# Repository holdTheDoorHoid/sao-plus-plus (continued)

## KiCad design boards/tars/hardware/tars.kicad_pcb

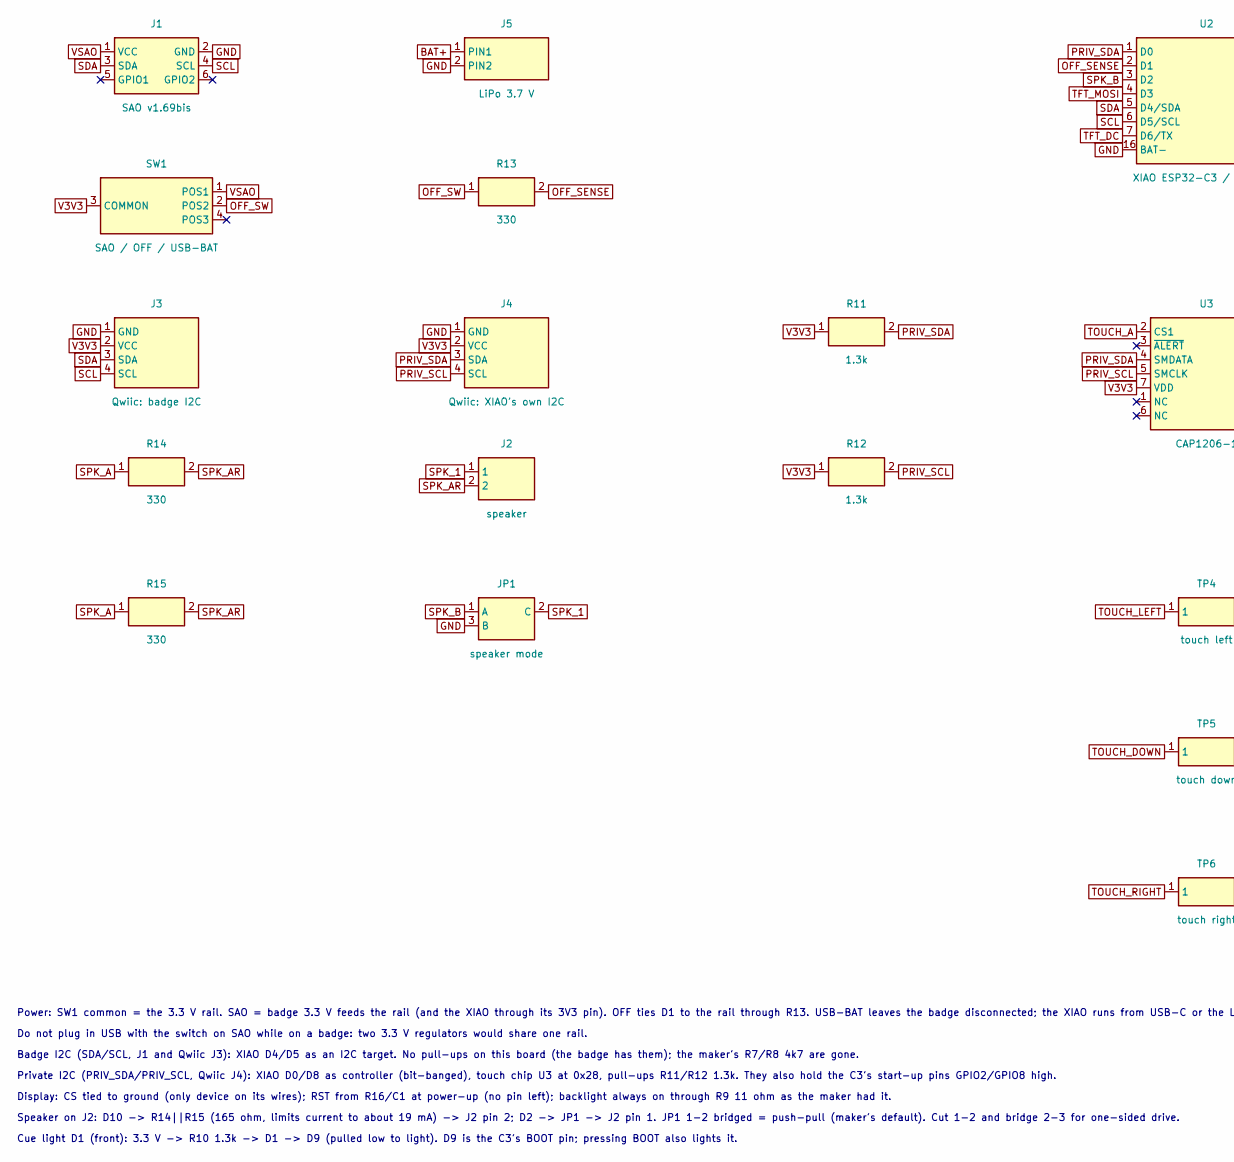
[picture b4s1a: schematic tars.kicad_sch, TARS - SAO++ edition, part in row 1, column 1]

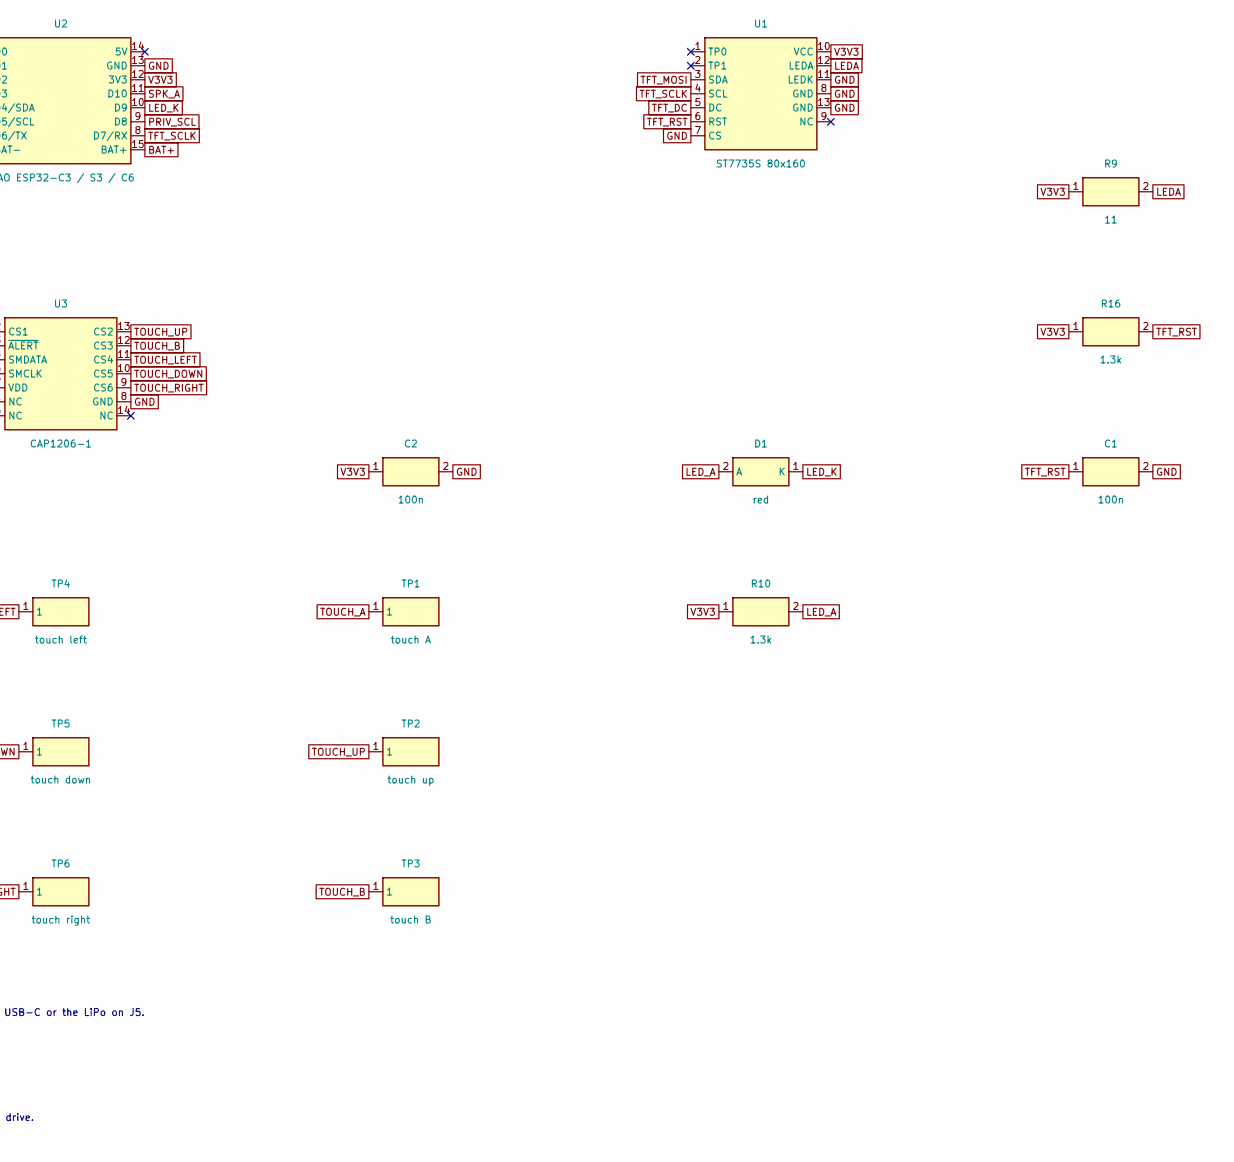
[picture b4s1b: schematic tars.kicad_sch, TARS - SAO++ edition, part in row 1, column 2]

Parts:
C1, C2: 100n; SAOPP_C_0603_1608Metric; MPN CC0603KRX7R9BB104; LCSC C14663
D1: red; LED_0603_1608Metric_Pad1.05x0.95mm_HandSolder; MPN LTST-C191KRKT; LCSC C125099
J1: SAO v1.69bis; SAOPP_CONN-01_BoxHeader_2x03_P2.54mm_SMD_XFCN_BH254VS-6P; MPN BH254VS-6P; LCSC C492445
J2: speaker; Molex_PicoBlade_53261-0271_1x02-1MP_P1.25mm_Horizontal; MPN 53261-0271; LCSC C177225
J3: Qwiic: badge I2C; JST_SH_SM04B-SRSS-TB_1x04-1MP_P1.00mm_Horizontal; MPN SM04B-SRSS-TB(LF)(SN); LCSC C160404
J4: Qwiic: XIAO's own I2C; JST_SH_SM04B-SRSS-TB_1x04-1MP_P1.00mm_Horizontal; MPN SM04B-SRSS-TB(LF)(SN); LCSC C160404
J5: LiPo 3.7 V; SAOPP_CONN-10_JST_PH_S2B-PH-SM4-TB_1x02_Horizontal; MPN S2B-PH-SM4-TB(LF)(SN); LCSC C295747
JP1: speaker mode; SolderJumper-3_P1.3mm_Bridged12_RoundedPad1.0x1.5mm; MPN none: solder jumper, nothing fitted
R9: 11; R_0603_1608Metric; MPN 0603WAF110JT5E
R10, R11, R12, R16: 1.3k; SAOPP_R_0603_1608Metric; MPN 0603WAF1301T5E; LCSC C22767
R13, R14, R15: 330; SAOPP_R_0603_1608Metric; MPN 0603WAF3300T5E; LCSC C23138
SW1: SAO / OFF / USB-BAT; SAOPP_SW-01_Slide_SP3T_CK_PCM13SMTR; MPN PCM13SMTR; LCSC C221842
TP1: touch A; TestPoint_Pad_D1.0mm; MPN none: bare copper inside a touch pad
TP2: touch up; TestPoint_Pad_D1.0mm; MPN none: bare copper inside a touch pad
TP3: touch B; TestPoint_Pad_D1.0mm; MPN none: bare copper inside a touch pad
TP4: touch left; TestPoint_Pad_D1.0mm; MPN none: bare copper inside a touch pad
TP5: touch down; TestPoint_Pad_D1.0mm; MPN none: bare copper inside a touch pad
TP6: touch right; TestPoint_Pad_D1.0mm; MPN none: bare copper inside a touch pad
U1: ST7735S 80x160; ST7735S-160x80-13PIN; MPN 0.96 in 80x160 ST7735S IPS, 13-pin 0.7 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
U2: XIAO ESP32-C3 / S3 / C6; SAOPP_MCU-01_Seeed_XIAO_SMD_C3_S3_C6; MPN XIAO ESP32-C3 / S3 / C6
U3: CAP1206-1; SOIC-14_3.9x8.7mm_P1.27mm; MPN CAP1206-1-SL-TR; LCSC C2652106

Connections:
BAT+: J5.1 (PIN1), U2.15 (BAT+)
GND: C1.2, C2.2, J1.2 (GND), J3.1 (GND), J4.1 (GND), J5.2 (PIN2), JP1.3 (B), U1.7 (CS), U1.8 (GND), U1.11 (LEDK), U1.13 (GND), U2.13 (GND), U2.16 (BAT-), U3.8 (GND)
LEDA: R9.2, U1.12 (LEDA)
LED_A: D1.2 (A), R10.2
LED_K: D1.1 (K), U2.10 (D9)
OFF_SENSE: R13.2, U2.2 (D1)
OFF_SW: R13.1, SW1.2 (POS2)
PRIV_SCL: J4.4 (SCL), R12.2, U2.9 (D8), U3.5 (SMCLK)
PRIV_SDA: J4.3 (SDA), R11.2, U2.1 (D0), U3.4 (SMDATA)
SCL: J1.4 (SCL), J3.4 (SCL), U2.6 (D5/SCL)
SDA: J1.3 (SDA), J3.3 (SDA), U2.5 (D4/SDA)
SPK_1: J2.1, JP1.2 (C)
SPK_A: R14.1, R15.1, U2.11 (D10)
SPK_AR: J2.2, R14.2, R15.2
SPK_B: JP1.1 (A), U2.3 (D2)
TFT_DC: U1.5 (DC), U2.7 (D6/TX)
TFT_MOSI: U1.3 (SDA), U2.4 (D3)
TFT_RST: C1.1, R16.2, U1.6 (RST)
TFT_SCLK: U1.4 (SCL), U2.8 (D7/RX)
TOUCH_A: TP1.1, U3.2 (CS1)
TOUCH_B: TP3.1, U3.12 (CS3)
TOUCH_DOWN: TP5.1, U3.10 (CS5)
TOUCH_LEFT: TP4.1, U3.11 (CS4)
TOUCH_RIGHT: TP6.1, U3.9 (CS6)
TOUCH_UP: TP2.1, U3.13 (CS2)
V3V3: C2.1, J3.2 (VCC), J4.2 (VCC), R9.1, R10.1, R11.1, R12.1, R16.1, SW1.3 (COMMON), U1.10 (VCC), U2.12 (3V3), U3.7 (VDD)
VSAO: J1.1 (VCC), SW1.1 (POS1)

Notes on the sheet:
Power: SW1 common = the 3.3 V rail. SAO = badge 3.3 V feeds the rail (and the XIAO through its 3V3 pin). OFF ties D1 to the rail through R13. USB-BAT leaves the badge disconnected; the XIAO runs from USB-C or the LiPo on J5.
Do not plug in USB with the switch on SAO while on a badge: two 3.3 V regulators would share one rail.
Badge I2C (SDA/SCL, J1 and Qwiic J3): XIAO D4/D5 as an I2C target. No pull-ups on this board (the badge has them); the maker's R7/R8 4k7 are gone.
Private I2C (PRIV_SDA/PRIV_SCL, Qwiic J4): XIAO D0/D8 as controller (bit-banged), touch chip U3 at 0x28, pull-ups R11/R12 1.3k. They also hold the C3's start-up pins GPIO2/GPIO8 high.
Display: CS tied to ground (only device on its wires); RST from R16/C1 at power-up (no pin left); backlight always on through R9 11 ohm as the maker had it.
Speaker on J2: D10 -> R14||R15 (165 ohm, limits current to about 19 mA) -> J2 pin 2; D2 -> JP1 -> J2 pin 1. JP1 1-2 bridged = push-pull (maker's default). Cut 1-2 and bridge 2-3 for one-sided drive.
Cue light D1 (front): 3.3 V -> R10 1.3k -> D1 -> D9 (pulled low to light). D9 is the C3's BOOT pin; pressing BOOT also lights it.

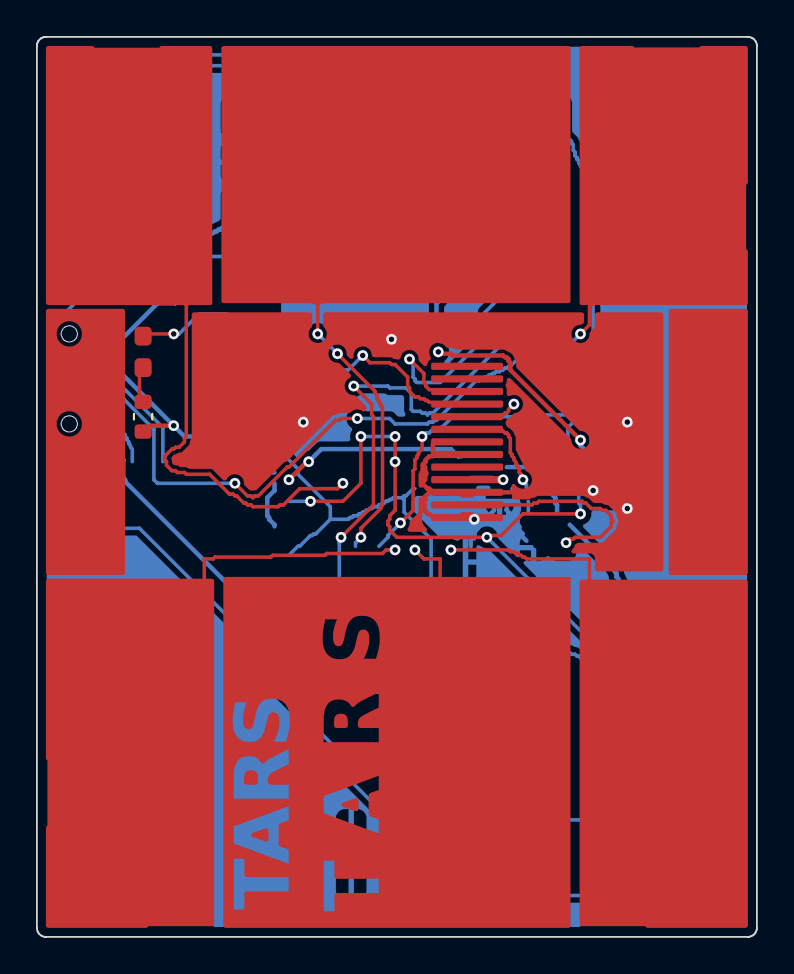
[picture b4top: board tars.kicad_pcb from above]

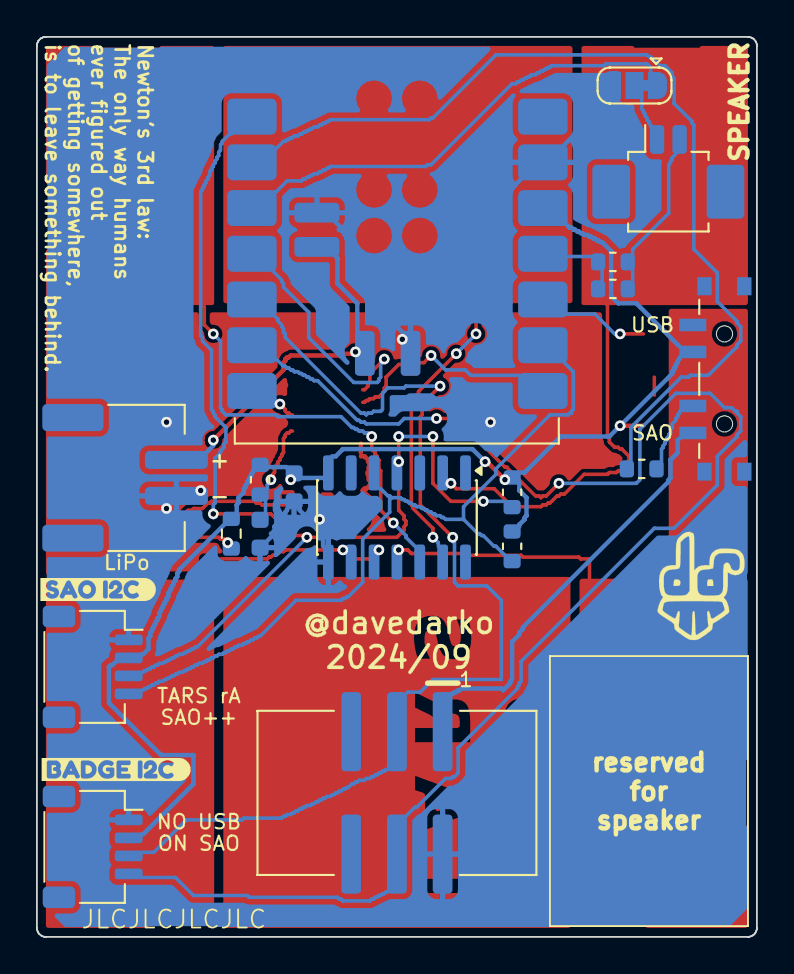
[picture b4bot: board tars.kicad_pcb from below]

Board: 2 copper layers, 40.0 x 50.0 mm, 30 parts (21 on the bottom side), 27 nets.

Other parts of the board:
Ref**: Val**; davedarko_logo_silk_outline
kibuzzard-66F128E4: G***; kibuzzard-66F128E4
kibuzzard-66F12846: G***; kibuzzard-66F12846

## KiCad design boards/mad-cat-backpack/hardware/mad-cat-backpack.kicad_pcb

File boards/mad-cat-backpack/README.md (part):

# Mad Cat Backpack — SAO++ edition

Originally the **Mad Cat Backpack** by **Wireb (Peter Shabino)**, 2018: https://github.com/Wireb/Mad_Cat_Backpack (commit f247c92). It is a small board that is soldered flat against the **back** of TwinkleTwinkie's Mad Cat SAO and makes the cat's eyes and teeth move: they fade, blink, "talk", lick their lips and sparkle.

> **Open licence (MIT).** The maker's design and firmware are MIT-licensed, so they may be copied, changed and sold, as long as his notice goes with them:
>
> *Copyright (c) 2018 Peter Shabino.* Permission is hereby granted, free of charge, to any person obtaining a copy of this hardware, software, and associated documentation files (the "Product"), to deal in the Product without restriction, including without limitation the rights to use, copy, modify, merge, publish, distribute, sublicense, and/or sell copies of the Product, and to permit persons to whom the Product is furnished to do so, subject to the following conditions: The above copyright notice and this permission notice shall be included in all copies or substantial portions of the Product. THE PRODUCT IS PROVIDED "AS IS", WITHOUT WARRANTY OF ANY KIND (full text: [original/LICENSE](original/LICENSE)).
>
> **Two things that are not his to license.** The little icon he drew on the back is a **Metroid**, a Nintendo character; it is kept exactly as he drew it, and whether to keep it is the owner's call. And this board exists to light **TwinkleTwinkie's Mad Cat** ([../mad-cat](../mad-cat)), whose own permission is still pending: this board carries none of the Mad Cat's art (only its outline and LED positions), but it is no use without one.

The renders show this board alone. The "front" is the side that is pressed against the back of the Mad Cat, so in use it is never seen; all the parts are on the other side, facing the badge.

## How it goes together with the Mad Cat

1. Build an SAO++ Mad Cat (**boards/mad-cat**) as a **bare board: fit none of its parts** (no connector, switch, cell clip, LEDs or resistors). It becomes the face plate.
2. Lay the bare Mad Cat face down and put this board on its back, parts side up. Line them up: each of this board's eight 1.0 mm light holes sits over one of the Mad Cat's bare eye or tooth windows, and the outlines match (this board is the Mad Cat's own outline, 0.35 mm smaller all round, so nothing shows from the front).
3. Solder the **eight bond holes** (the bare gold rings beside the eyes and the two middle-left teeth) from this side: solder fed into each hole runs down and joins the Mad Cat's unused LED pad underneath.
4. Plug the pair into a badge with this board's connector. It sits exactly where a plain Mad Cat's connector would, so the cat hangs the same way, just 1.6 mm further out.

The maker did the same thing in 2018 with an unmodified Mad Cat: he moved its eight LEDs onto his backpack, cut four of the Mad Cat's traces, and soldered four pads under the backpack's edge. On the SAO++ Mad Cat nothing has to be cut: leaving its parts off is enough.

**Can our Mad Cat still be driven by it?** Yes, that is what it is built for: the SAO++ Mad Cat kept the 2018 LED positions, and its back copper is already cleared around each one, so this board's LEDs shine through the same windows the Mad Cat's own LEDs would. A **2018** Mad Cat (with its LEDs and header removed) should light up the same way, but the bond holes would not land on its pads (its LED pads are 2.4 mm from each centre, not 1.55 mm), so it would need glue instead of solder. That has not been checked.

## What changed from the original

| | Original (2018) | SAO++ rev A |
|---|---|---|
| Size and shape | 33.5 × 31.2 mm plate behind the face only | **63.0 × 39.0 mm**: the Mad Cat's own outline, 0.35 mm smaller all round, covering the face, the haunch and the root of the tail. Bigger because the XIAO module (21 × 18 mm) does not fit behind the face with the eight LEDs |
| Controller | PIC16F1503 | **Seeed Studio XIAO ESP32** (C3, S3 or C6) on the back of the haunch, USB-C at the haunch's right-hand edge |
| Firmware | his PIC assembly | **new Rust firmware** that replays his eight animations with his timing and his random weights ([firmware/](firmware/)) |
| LEDs | the eight white TOPLEDs taken off the Mad Cat, on the side facing the cat | eight white **reverse-mount** LEDs (the shared SAO++ part) on the back, each over a 1.0 mm hole; same eight spots, same order |
| LED resistors | 8 × 200 Ω 0805 | 8 × **330 Ω** 0603 (shared part): about 1.5 mA per LED on 3.3 V, much like his board on badge power (he warned 200 Ω was "borderline too bright" on 5 V USB) |
| Power and connector | 4-pin header pushed through both boards (badge power), or his mini-USB socket | **6-pin SAO v1.69bis** shrouded connector on the back, in the Mad Cat connector's exact spot; **SAO / OFF / USB-BAT** slide switch with its knob out of the bottom edge under the left paw; **LiPo socket** (JST-PH) at the root of the tail, charged by the XIAO |
| Joining the boards | four pads soldered under the backpack's edge, four Mad Cat traces cut | **eight bond holes** over eight unused Mad Cat LED pads; nothing cut |
| I2C | none (his SDA/SCL holes went nowhere) | the XIAO is an I2C target at **0x24**: a badge can set the LEDs or start any animation |
| Dropped | — | the PIC, its programming header, mini-USB socket and 10 µF capacitor (the XIAO has its own) |
| Maker's art | "Mad Cat Backpack / PJS 17Oct2018 V0 / MIT license" lettering and a Metroid icon, both on the back near the old 4-pin header | **Both kept, unchanged in wording, size and shape, but moved**: the lettering to the middle of the face area (now horizontal), the icon to the root of the tail. Their old spot is under the new connector. He also drew the whole MIT notice in copper and silkscreen **outside** the board outline (it would never have been made); it is not on the board, and lives in `original/LICENSE` and above |

**Parts:** all shared SAO++ parts: the connector, switch, XIAO footprint, LiPo socket, the white reverse-mount LED (same as the Mad Cat's) and the 330 Ω resistor. **No new parts.** The bond holes and light holes are just holes.

## Power

| Knob | Badge 3.3 V | What runs the board |
|---|---|---|
| **SAO** | feeds the XIAO's 3V3 pin and the LEDs | the badge |
| **OFF** (middle) | disconnected | nothing from the badge. With USB or a LiPo attached, the switch pulls D1 high and the firmware puts everything dark and sleeps |
| **USB/BAT** | disconnected | the XIAO's own regulator, from USB-C or the LiPo |

- **Do not plug in USB while the knob is on SAO and the board is on a badge** (two 3.3 V regulators would be joined). It is printed on the back.
- **Current from the badge:** LEDs at most about 12 mA (all eight full on, which is the cat's resting face) plus the XIAO with its radio off, about 15–25 mA for a C3 or C6 at 80 MHz (more for an S3). About 30–40 mA in all, inside the 50 mA SAO++ budget. Prefer a C3 or C6 for badge power.
- No coin cell (house rule for boards with a XIAO).

## Pin map

| XIAO pin | Goes to | Why this pin |
|---|---|---|
| D8 | left eye (D1) | free pin. On the C3 it is a start-up pin that must not be held low at power-on; the LED can only pull it **up** toward 3.3 V, the safe direction |
| D7 | right eye (D2) | house job is SAO GPIO1, unused here (the 2018 board had a 4-pin SAO), so it drives an LED |
| D9 | tooth 1 (D3) | on the C3 this is also the module's **BOOT button**; the firmware drives it open-drain (only ever pulls low) and reads the button between dimming frames. Same start-up note as D8 |
| D10 | tooth 2 (D4) | house job is addressable-LED data; there are none here |
| D0 | tooth 3 (D5) | free pin (C3 start-up pin: same note as D8) |
| D2 | tooth 4 (D6) | free pin |
| D3 | tooth 5 (D7) | free pin |
| D6 | tooth 6 (D8) | house job is SAO GPIO2, unused here. On the C3 and S3 this is the chip's serial-console TX pin, so tooth 6 may flicker for a moment while the module starts up |
| D4 / D5 | SAO SDA / SCL | house pins; the XIAO is the badge's I2C target (no pull-ups on the board) |
| D1 | switch OFF sense | house pin: high when the knob is on OFF |
| 3V3, GND | the 3.3 V rail (switch common, the eight LED resistors) and ground | |
| BAT+ / BAT− (under the module, both positions) | the LiPo socket | |
| 5V | not connected | |

**Why every pin is used, and why there is no expander chip:** eight LEDs that each fade on their own need eight pins (his animations dim every LED separately). The XIAO has eleven; I2C (D4/D5) and the OFF sense (D1) keep their house jobs, which leaves eight. To get there the two SAO GPIO pins are not connected (the original never had them), the addressable-LED pin drives a plain LED, and one LED shares a pin with the BOOT button. All four start-up ("strapping") pins of the C3 that are used here only ever see an LED to 3.3 V, which can never pull them low at power-on. An LED driver chip (the shared IS31FL3731 that Do Or Donut uses) would have freed the pins, but it is a 28-pin part that would not fit with the XIAO behind a cat's face, and would cost a part for no visible gain.

Each LED: 3.3 V → 330 Ω → LED → XIAO pin. A pin driven **low** lights the LED, as on the maker's board.

## How it is wired

Everything is on the back except a ground plane, three short tracks and **11 tented vias** on the hidden front: three for the 3.3 V rail (it reaches the two groups of LEDs and the XIAO's 3V3 pin over the front), two for SCL, three for the LiPo's plus (its pads are under the module, boxed in by tracks), and three ground vias. The eight bond holes are also ground connections between the two sides. The eight LED tracks run in one bundle from the XIAO across the haunch into the middle of the face and branch to each LED; the 3.3 V rail runs round the outside (over the eyes, down the left cheek, under the teeth). On a board whose front is art these vias would be avoided; here the front is pressed against the Mad Cat and is never seen.

## Firmware

New Rust firmware is in [`firmware/`](firmware/) (37 tests pass; it builds for the C3, C6 and S3; **it has never run on a real board**). The default mode is the maker's show, worked out from his PIC program (`original/mplab/mad_cat_backpack_v0.asm`): after power-on the smile fades in and then the eyes; then, over and over, all eight stay lit for a random 0–33 s and one of his eight animations plays, chosen with his weights (blink most often, sparkles least). The BOOT button steps through two extra modes (all eight animations in turn; all steadily on), and a badge can take over through I2C. His readme says the wait is "0 to 8 minutes"; his code waits at most about 33 s, and the firmware follows the code.

## Things to check on the first prototype

1. **Light through two boards.** Each LED shines through its 1.0 mm hole into the back of the Mad Cat and out through the Mad Cat's bare-board window. Check the eyes and teeth are bright enough in room light, and that light does not leak sideways into the neighbouring windows. 330 Ω is already the lowest shared resistor; if the eyes are too dim, a lower value would be a new part (the firmware already runs them at full when they are "on").
2. **Bonding the two boards.** Solder fed into the eight bond holes must reach the Mad Cat's pads; the boards must sit flat against each other (nothing fitted on the Mad Cat's back). Check the joint holds when the stack is knocked. If not, add a thin layer of double-sided tape between the boards before soldering.
3. **Alignment.** Look through the light holes before soldering: each should show the Mad Cat's window. The two boards share coordinates, so the holes and outlines line up if the boards do.
4. **Badge power into the XIAO's 3V3 pin** (as on Hack-Man and Mr. Robot): boots from a badge alone, nothing gets warm, under 50 mA with all LEDs on.
5. **Switch knob** under the left paw: it ends within about 0.1 mm of the paws' bottom edge, so it is reached from below, between the cat and the badge. Check it is easy to slide and does not show from the front. Which way is SAO is not drawn in the switch's datasheet; if SAO and USB/BAT turn out swapped, the silkscreen is wrong, not the wiring.
6. **The switch's two locating pegs** go through this board toward the Mad Cat. If they stick out past 1.6 mm they will press on the Mad Cat's back; trim them if so.
7. **USB-C plug** at the haunch's right edge: it goes in between the cat and the badge. The socket stays about 0.5 mm inside the Mad Cat's outline. Check a plug seats fully.
8. **LiPo polarity**: the socket follows the Adafruit / SparkFun convention ("+" printed beside it). Check each cell with a meter first. Its pads under the XIAO only solder with paste and hot air, a hot plate or the assembler.
9. **Connector and pin 1** against a v1.69bis badge (same spot and orientation as the SAO++ Mad Cat's).
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
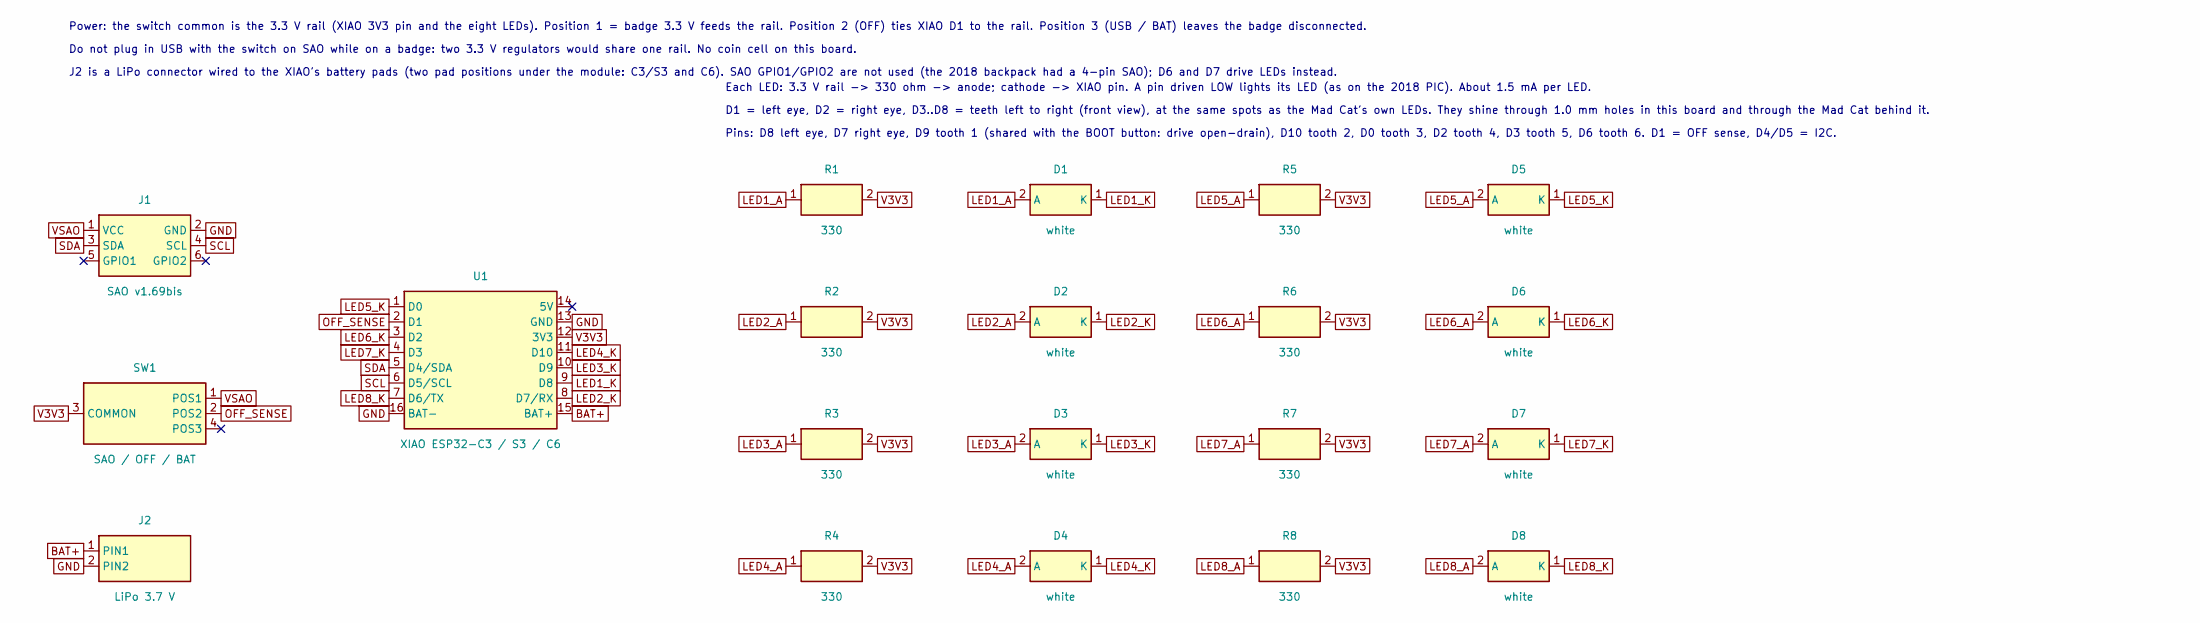
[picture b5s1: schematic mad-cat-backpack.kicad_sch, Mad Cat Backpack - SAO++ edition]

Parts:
D1, D2, D3, D4, D5, D6, D7, D8: white; SAOPP_LED-10_1206_ReverseMount_ThroughBoard; MPN LTW-C230DS; LCSC C575513
J1: SAO v1.69bis; SAOPP_CONN-01_BoxHeader_2x03_P2.54mm_SMD_XFCN_BH254VS-6P; MPN BH254VS-6P; LCSC C492445
J2: LiPo 3.7 V; SAOPP_CONN-10_JST_PH_S2B-PH-SM4-TB_1x02_Horizontal; MPN S2B-PH-SM4-TB(LF)(SN); LCSC C295747
R1, R2, R3, R4, R5, R6, R7, R8: 330; SAOPP_R_0603_1608Metric; MPN 0603WAF3300T5E; LCSC C23138
SW1: SAO / OFF / BAT; SAOPP_SW-01_Slide_SP3T_CK_PCM13SMTR; MPN PCM13SMTR; LCSC C221842
U1: XIAO ESP32-C3 / S3 / C6; SAOPP_MCU-01_Seeed_XIAO_SMD_C3_S3_C6; MPN XIAO ESP32-C3 / S3 / C6

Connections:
BAT+: J2.1 (PIN1), U1.15 (BAT+)
GND: J1.2 (GND), J2.2 (PIN2), U1.13 (GND), U1.16 (BAT-)
LED1_A: D1.2 (A), R1.1
LED1_K: D1.1 (K), U1.9 (D8)
LED2_A: D2.2 (A), R2.1
LED2_K: D2.1 (K), U1.8 (D7/RX)
LED3_A: D3.2 (A), R3.1
LED3_K: D3.1 (K), U1.10 (D9)
LED4_A: D4.2 (A), R4.1
LED4_K: D4.1 (K), U1.11 (D10)
LED5_A: D5.2 (A), R5.1
LED5_K: D5.1 (K), U1.1 (D0)
LED6_A: D6.2 (A), R6.1
LED6_K: D6.1 (K), U1.3 (D2)
LED7_A: D7.2 (A), R7.1
LED7_K: D7.1 (K), U1.4 (D3)
LED8_A: D8.2 (A), R8.1
LED8_K: D8.1 (K), U1.7 (D6/TX)
OFF_SENSE: SW1.2 (POS2), U1.2 (D1)
SCL: J1.4 (SCL), U1.6 (D5/SCL)
SDA: J1.3 (SDA), U1.5 (D4/SDA)
V3V3: R1.2, R2.2, R3.2, R4.2, R5.2, R6.2, R7.2, R8.2, SW1.3 (COMMON), U1.12 (3V3)
VSAO: J1.1 (VCC), SW1.1 (POS1)

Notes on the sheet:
Power: the switch common is the 3.3 V rail (XIAO 3V3 pin and the eight LEDs). Position 1 = badge 3.3 V feeds the rail. Position 2 (OFF) ties XIAO D1 to the rail. Position 3 (USB / BAT) leaves the badge disconnected.
Do not plug in USB with the switch on SAO while on a badge: two 3.3 V regulators would share one rail. No coin cell on this board.
J2 is a LiPo connector wired to the XIAO's battery pads (two pad positions under the module: C3/S3 and C6). SAO GPIO1/GPIO2 are not used (the 2018 backpack had a 4-pin SAO); D6 and D7 drive LEDs instead.
Each LED: 3.3 V rail -> 330 ohm -> anode; cathode -> XIAO pin. A pin driven LOW lights its LED (as on the 2018 PIC). About 1.5 mA per LED.
D1 = left eye, D2 = right eye, D3..D8 = teeth left to right (front view), at the same spots as the Mad Cat's own LEDs. They shine through 1.0 mm holes in this board and through the Mad Cat behind it.
Pins: D8 left eye, D7 right eye, D9 tooth 1 (shared with the BOOT button: drive open-drain), D10 tooth 2, D0 tooth 3, D2 tooth 4, D3 tooth 5, D6 tooth 6. D1 = OFF sense, D4/D5 = I2C.

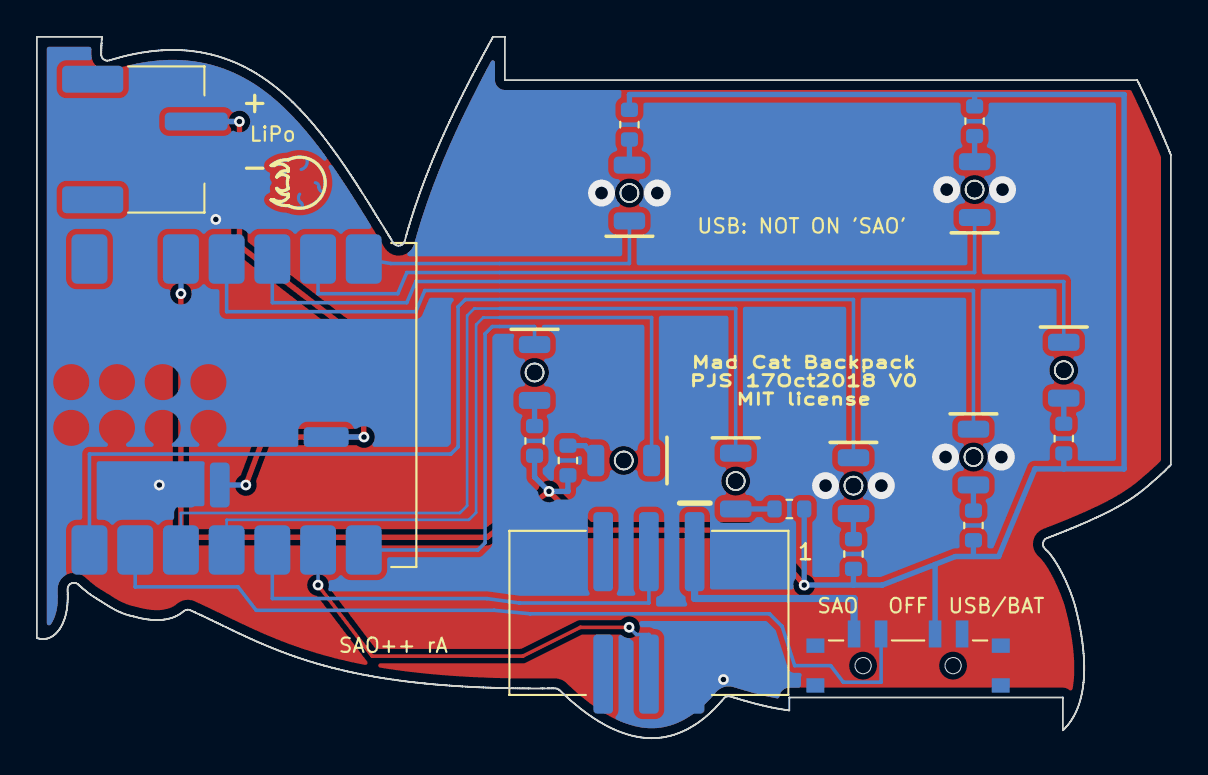
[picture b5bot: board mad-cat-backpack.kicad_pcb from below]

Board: 2 copper layers, 63.0 x 39.0 mm, 20 parts (20 on the bottom side), 23 nets.

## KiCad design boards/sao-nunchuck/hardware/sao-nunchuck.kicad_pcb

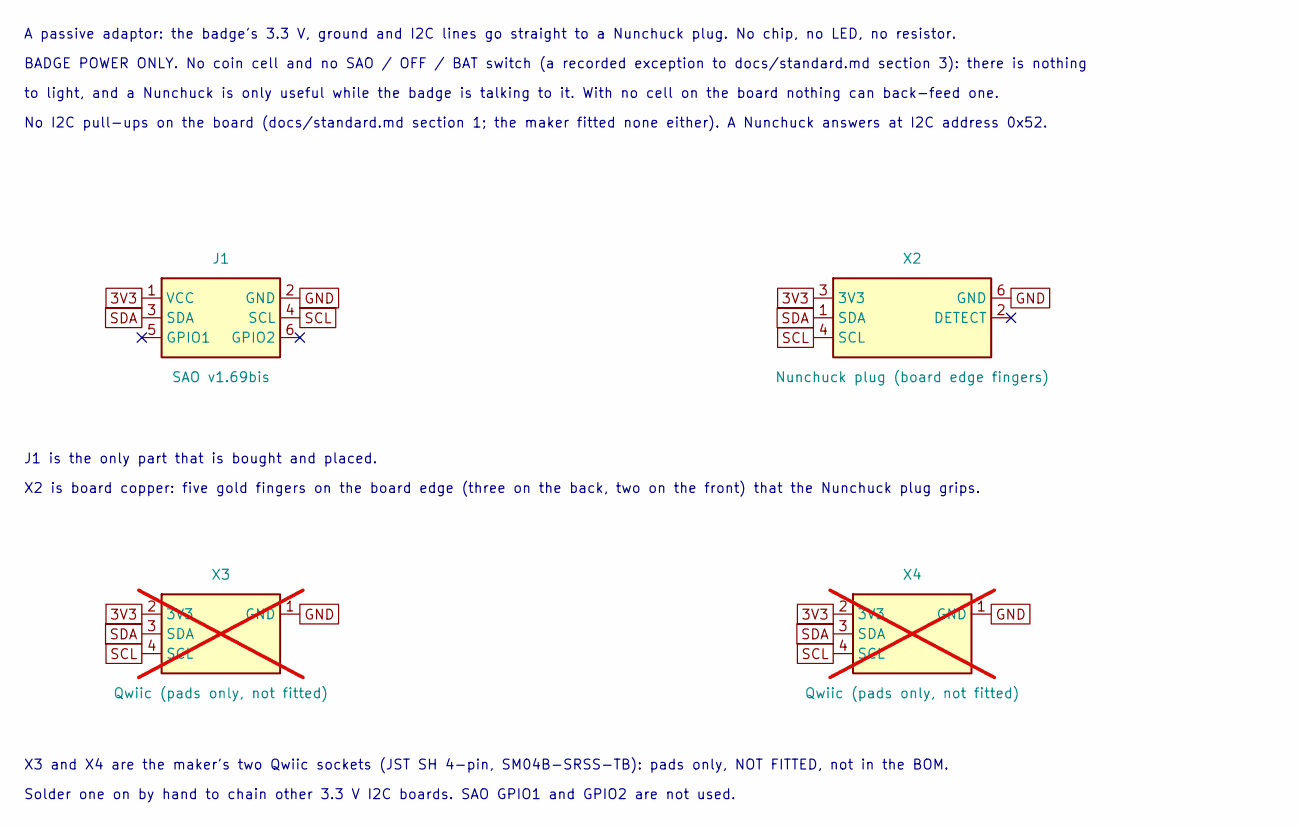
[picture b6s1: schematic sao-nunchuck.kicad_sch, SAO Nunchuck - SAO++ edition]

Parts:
J1: SAO v1.69bis; SAOPP_CONN-01_BoxHeader_2x03_P2.54mm_SMD_XFCN_BH254VS-6P; MPN BH254VS-6P; LCSC C492445
X2: Nunchuck plug (board edge fingers); Nunchuck_Plug_EdgeFingers; MPN none: PCB copper, nothing fitted
X3, X4: Qwiic (pads only, not fitted); Qwiic_JST_SH_SM04B-SRSS-TB_NotFitted; MPN SM04B-SRSS-TB; LCSC C160404; not fitted

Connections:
3V3: J1.1 (VCC), X2.3 (3V3), X3.2 (3V3), X4.2 (3V3)
GND: J1.2 (GND), X2.6 (GND), X3.1 (GND), X4.1 (GND)
SCL: J1.4 (SCL), X2.4 (SCL), X3.4 (SCL), X4.4 (SCL)
SDA: J1.3 (SDA), X2.1 (SDA), X3.3 (SDA), X4.3 (SDA)

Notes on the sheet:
A passive adaptor: the badge's 3.3 V, ground and I2C lines go straight to a Nunchuck plug. No chip, no LED, no resistor.
BADGE POWER ONLY. No coin cell and no SAO / OFF / BAT switch (a recorded exception to docs/standard.md section 3): there is nothing
to light, and a Nunchuck is only useful while the badge is talking to it. With no cell on the board nothing can back-feed one.
No I2C pull-ups on the board (docs/standard.md section 1; the maker fitted none either). A Nunchuck answers at I2C address 0x52.
J1 is the only part that is bought and placed.
X2 is board copper: five gold fingers on the board edge (three on the back, two on the front) that the Nunchuck plug grips.
X3 and X4 are the maker's two Qwiic sockets (JST SH 4-pin, SM04B-SRSS-TB): pads only, NOT FITTED, not in the BOM.
Solder one on by hand to chain other 3.3 V I2C boards. SAO GPIO1 and GPIO2 are not used.

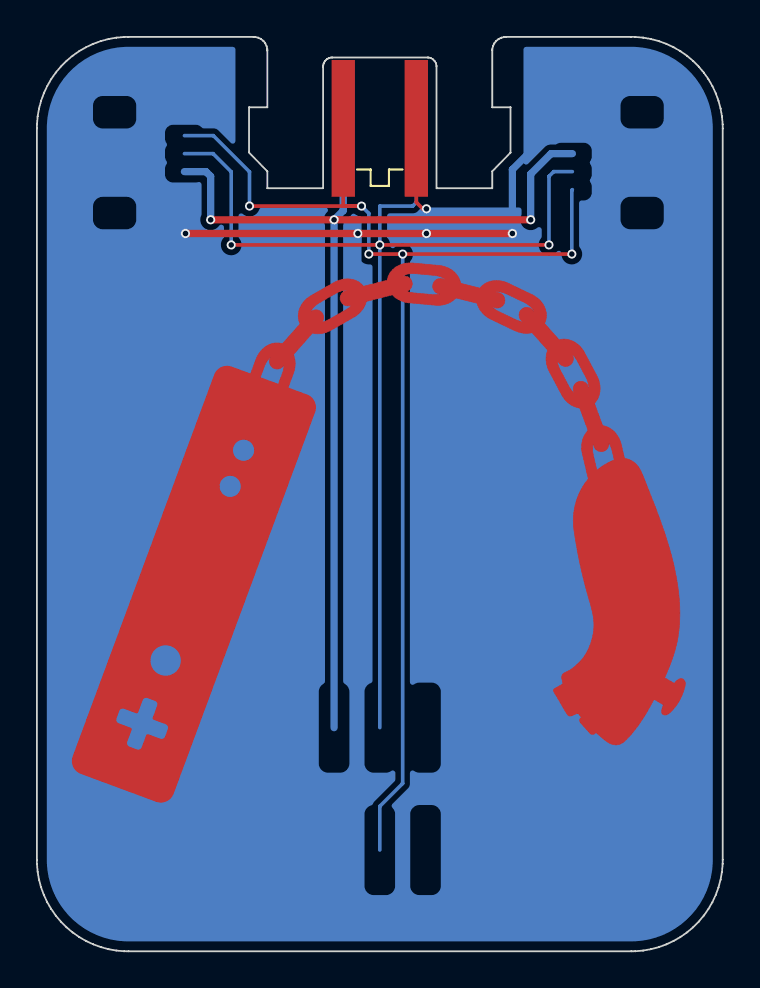
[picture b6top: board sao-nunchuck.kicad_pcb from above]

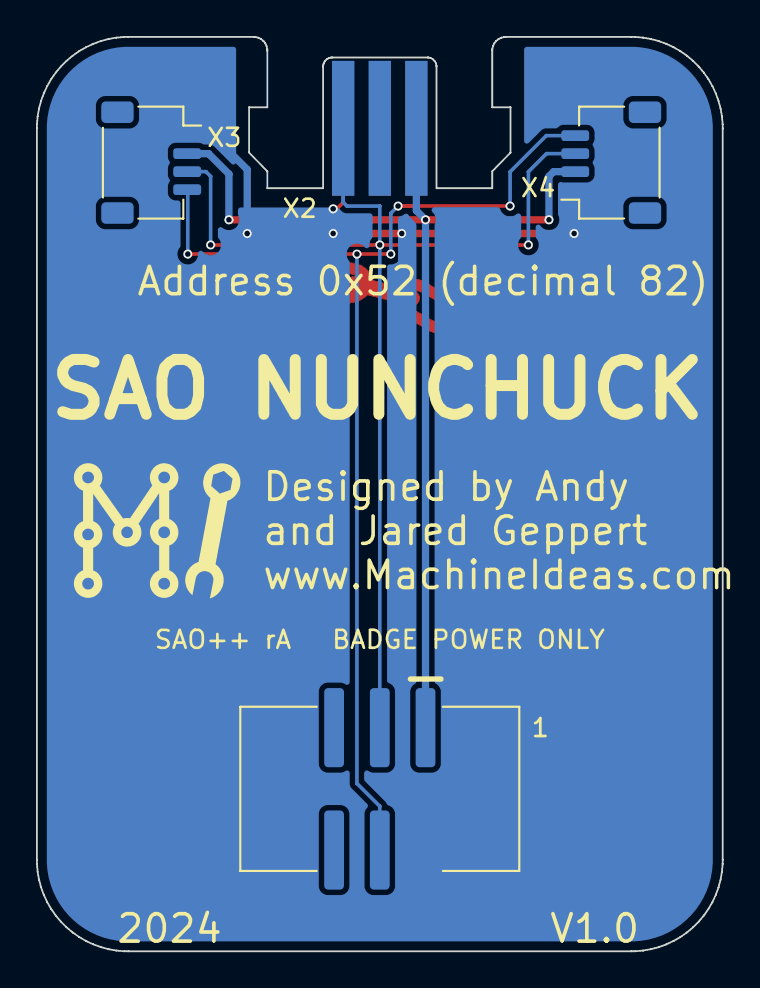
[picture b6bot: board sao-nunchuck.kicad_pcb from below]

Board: 2 copper layers, 38.1 x 50.8 mm, 5 parts (4 on the bottom side), 4 nets.

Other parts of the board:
L1: Machine_Ideas_logo

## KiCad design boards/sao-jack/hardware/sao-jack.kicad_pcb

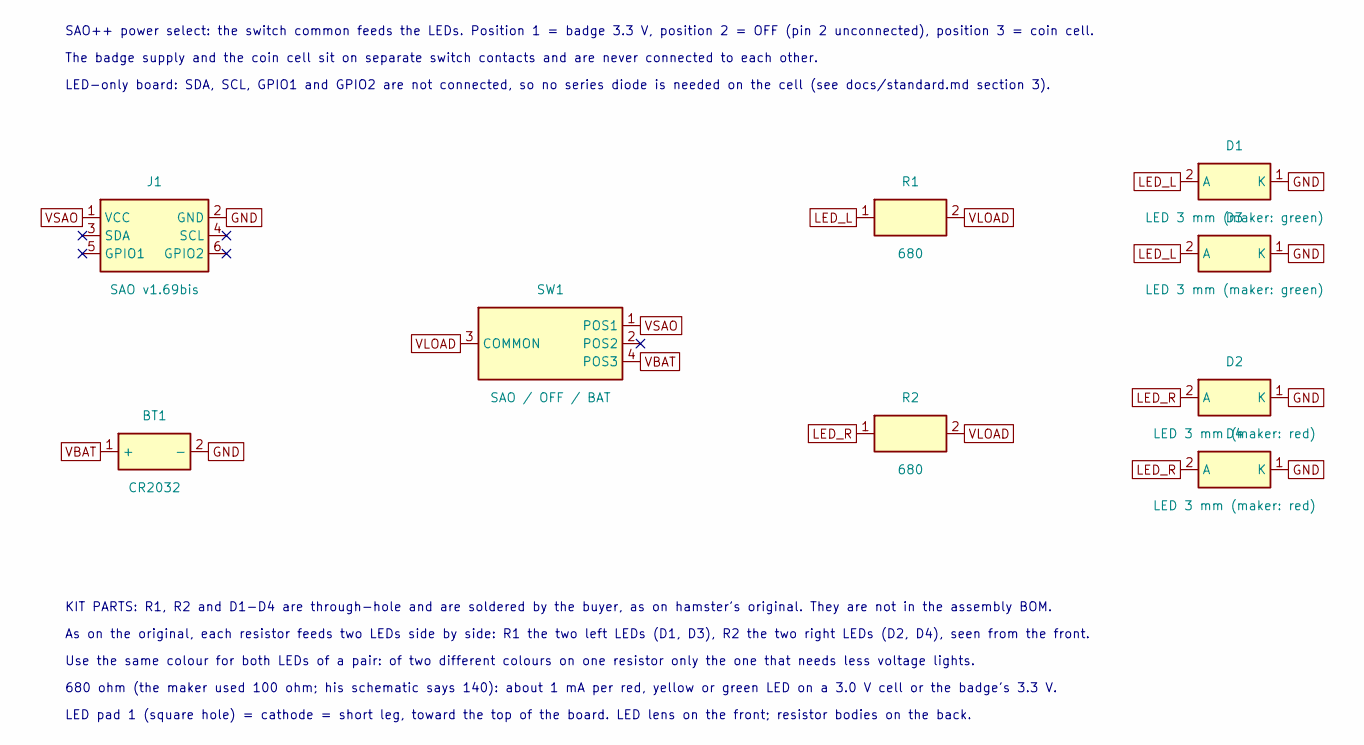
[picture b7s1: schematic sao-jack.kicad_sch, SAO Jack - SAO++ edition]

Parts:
BT1: CR2032; SAOPP_BAT-01_CR2032_SMD_TE_BAT-HLD-001; MPN BAT-HLD-001; LCSC C7501066
D1, D3: LED 3 mm (maker: green); LED_D3.0mm; MPN kit part, not chosen: any 3 mm (T-1) LE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
D2, D4: LED 3 mm (maker: red); LED_D3.0mm; MPN kit part, not chosen: any 3 mm (T-1) LE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
J1: SAO v1.69bis; SAOPP_CONN-01_BoxHeader_2x03_P2.54mm_SMD_XFCN_BH254VS-6P; MPN BH254VS-6P; LCSC C492445
R1, R2: 680; R_Axial_DIN0204_L3.6mm_D1.6mm_P7.62mm_Horizontal; MPN kit part, not chosen: any 680 ohm 1/8 W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
SW1: SAO / OFF / BAT; SAOPP_SW-01_Slide_SP3T_CK_PCM13SMTR; MPN PCM13SMTR; LCSC C221842

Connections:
GND: BT1.2 (-), D1.1 (K), D2.1 (K), D3.1 (K), D4.1 (K), J1.2 (GND)
LED_L: D1.2 (A), D3.2 (A), R1.1
LED_R: D2.2 (A), D4.2 (A), R2.1
VBAT: BT1.1 (+), SW1.4 (POS3)
VLOAD: R1.2, R2.2, SW1.3 (COMMON)
VSAO: J1.1 (VCC), SW1.1 (POS1)

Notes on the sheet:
SAO++ power select: the switch common feeds the LEDs. Position 1 = badge 3.3 V, position 2 = OFF (pin 2 unconnected), position 3 = coin cell.
The badge supply and the coin cell sit on separate switch contacts and are never connected to each other.
LED-only board: SDA, SCL, GPIO1 and GPIO2 are not connected, so no series diode is needed on the cell (see docs/standard.md section 3).
KIT PARTS: R1, R2 and D1-D4 are through-hole and are soldered by the buyer, as on hamster's original. They are not in the assembly BOM.
As on the original, each resistor feeds two LEDs side by side: R1 the two left LEDs (D1, D3), R2 the two right LEDs (D2, D4), seen from the front.
Use the same colour for both LEDs of a pair: of two different colours on one resistor only the one that needs less voltage lights.
680 ohm (the maker used 100 ohm; his schematic says 140): about 1 mA per red, yellow or green LED on a 3.0 V cell or the badge's 3.3 V.
LED pad 1 (square hole) = cathode = short leg, toward the top of the board. LED lens on the front; resistor bodies on the back.

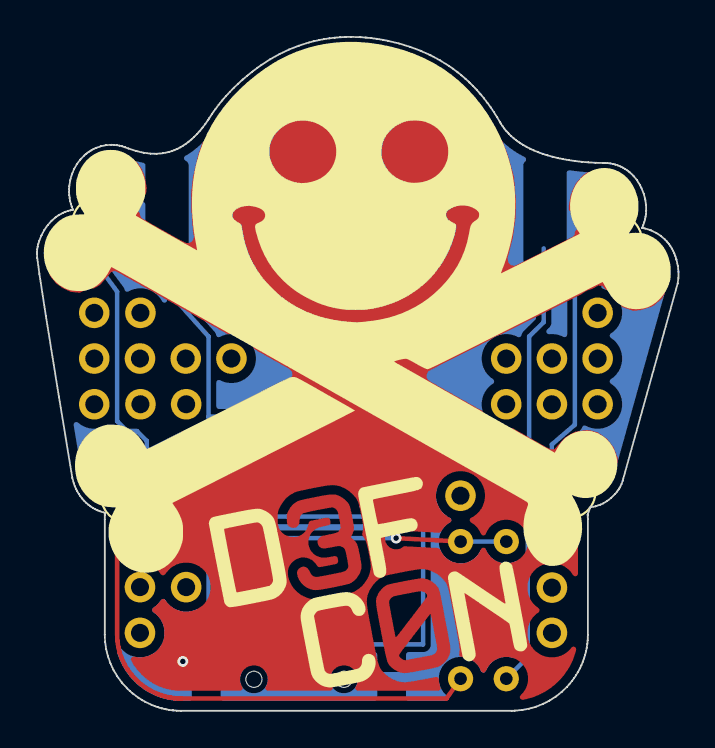
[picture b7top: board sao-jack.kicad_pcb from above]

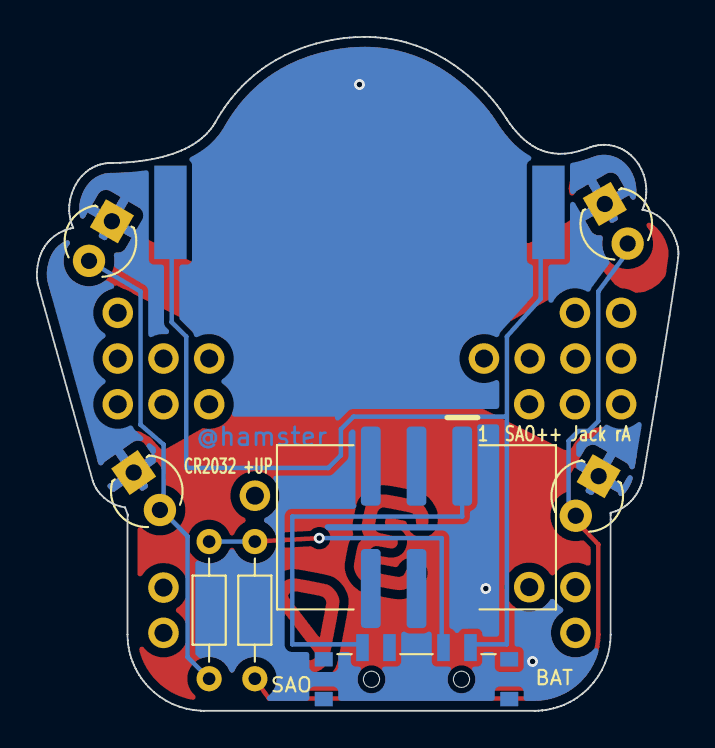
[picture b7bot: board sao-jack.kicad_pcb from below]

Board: 2 copper layers, 35.6 x 37.4 mm, 9 parts (5 on the bottom side), 6 nets.

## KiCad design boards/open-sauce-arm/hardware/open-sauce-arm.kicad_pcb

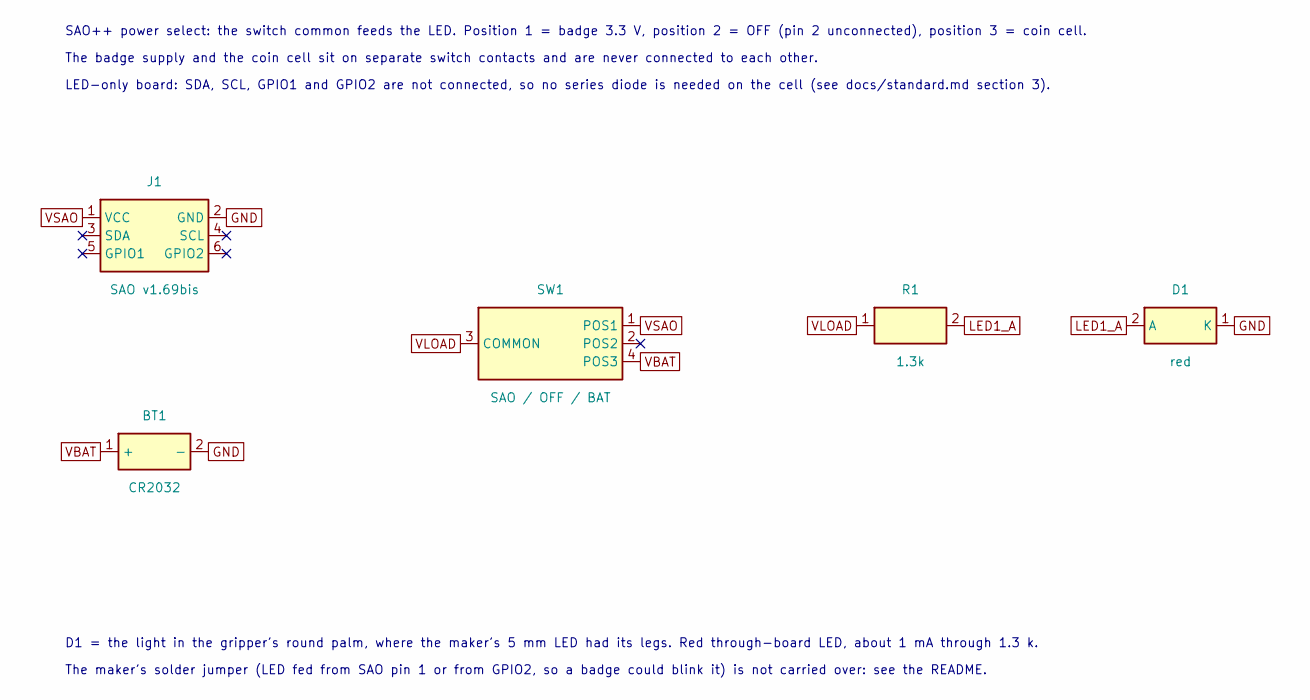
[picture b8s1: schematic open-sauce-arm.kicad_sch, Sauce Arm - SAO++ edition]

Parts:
BT1: CR2032; SAOPP_BAT-01_CR2032_SMD_TE_BAT-HLD-001; MPN BAT-HLD-001; LCSC C7501066
D1: red; SAOPP_LED-10_1206_ReverseMount_ThroughBoard; MPN LTST-C230KRKT; LCSC C125107
J1: SAO v1.69bis; SAOPP_CONN-01_BoxHeader_2x03_P2.54mm_SMD_XFCN_BH254VS-6P; MPN BH254VS-6P; LCSC C492445
R1: 1.3k; SAOPP_R_0603_1608Metric; MPN 0603WAF1301T5E; LCSC C22767
SW1: SAO / OFF / BAT; SAOPP_SW-01_Slide_SP3T_CK_PCM13SMTR; MPN PCM13SMTR; LCSC C221842

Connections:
GND: BT1.2 (-), D1.1 (K), J1.2 (GND)
LED1_A: D1.2 (A), R1.2
VBAT: BT1.1 (+), SW1.4 (POS3)
VLOAD: R1.1, SW1.3 (COMMON)
VSAO: J1.1 (VCC), SW1.1 (POS1)

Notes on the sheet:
SAO++ power select: the switch common feeds the LED. Position 1 = badge 3.3 V, position 2 = OFF (pin 2 unconnected), position 3 = coin cell.
The badge supply and the coin cell sit on separate switch contacts and are never connected to each other.
LED-only board: SDA, SCL, GPIO1 and GPIO2 are not connected, so no series diode is needed on the cell (see docs/standard.md section 3).
D1 = the light in the gripper's round palm, where the maker's 5 mm LED had its legs. Red through-board LED, about 1 mA through 1.3 k.
The maker's solder jumper (LED fed from SAO pin 1 or from GPIO2, so a badge could blink it) is not carried over: see the README.

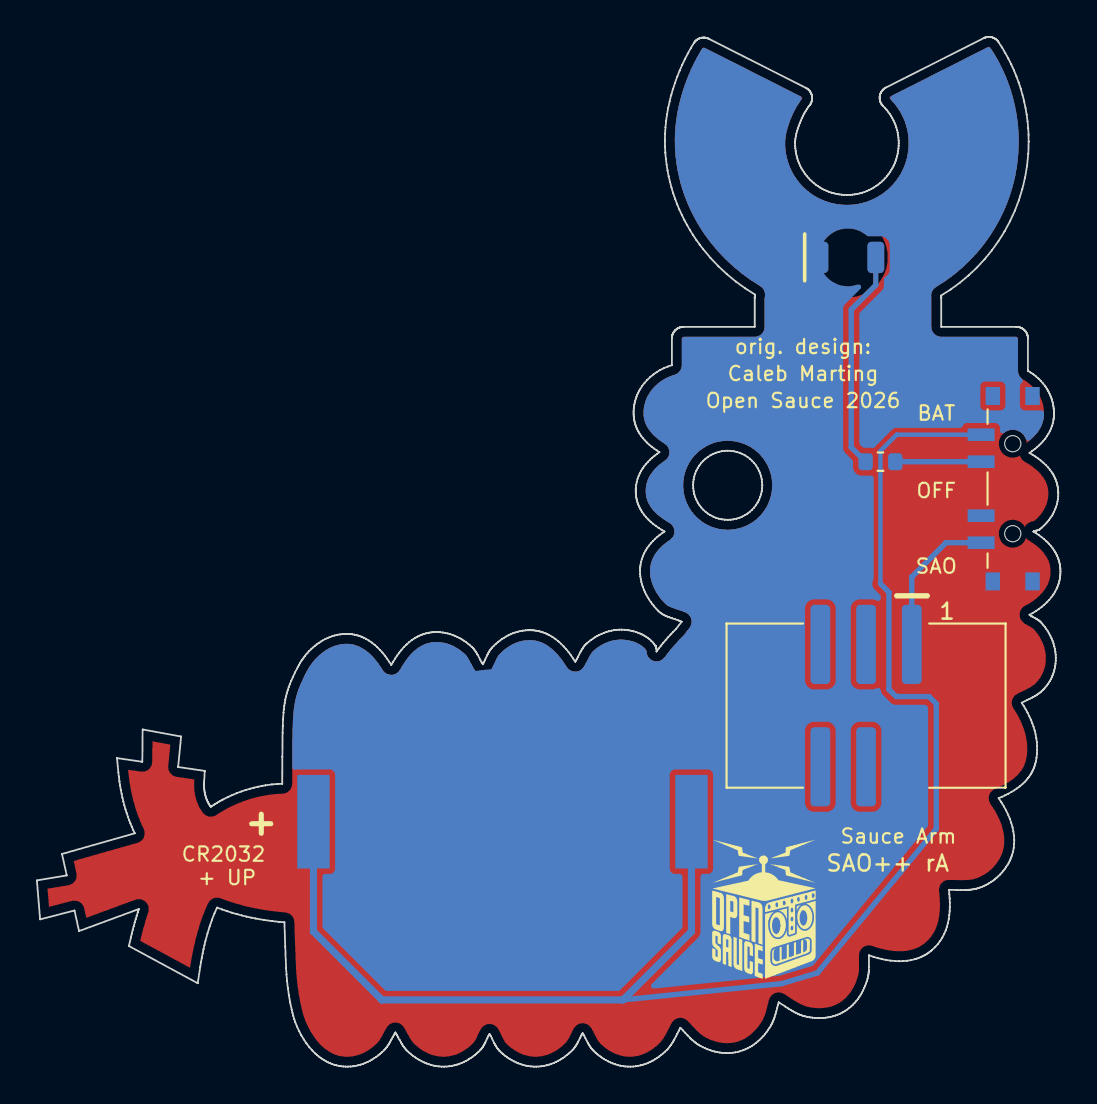
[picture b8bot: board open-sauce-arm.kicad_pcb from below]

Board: 2 copper layers, 56.9 x 57.2 mm, 5 parts (5 on the bottom side), 5 nets.
